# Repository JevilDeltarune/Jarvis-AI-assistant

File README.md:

# Jarvis-AI-assistant
A custom alexa type assistant using xiaozhi ai

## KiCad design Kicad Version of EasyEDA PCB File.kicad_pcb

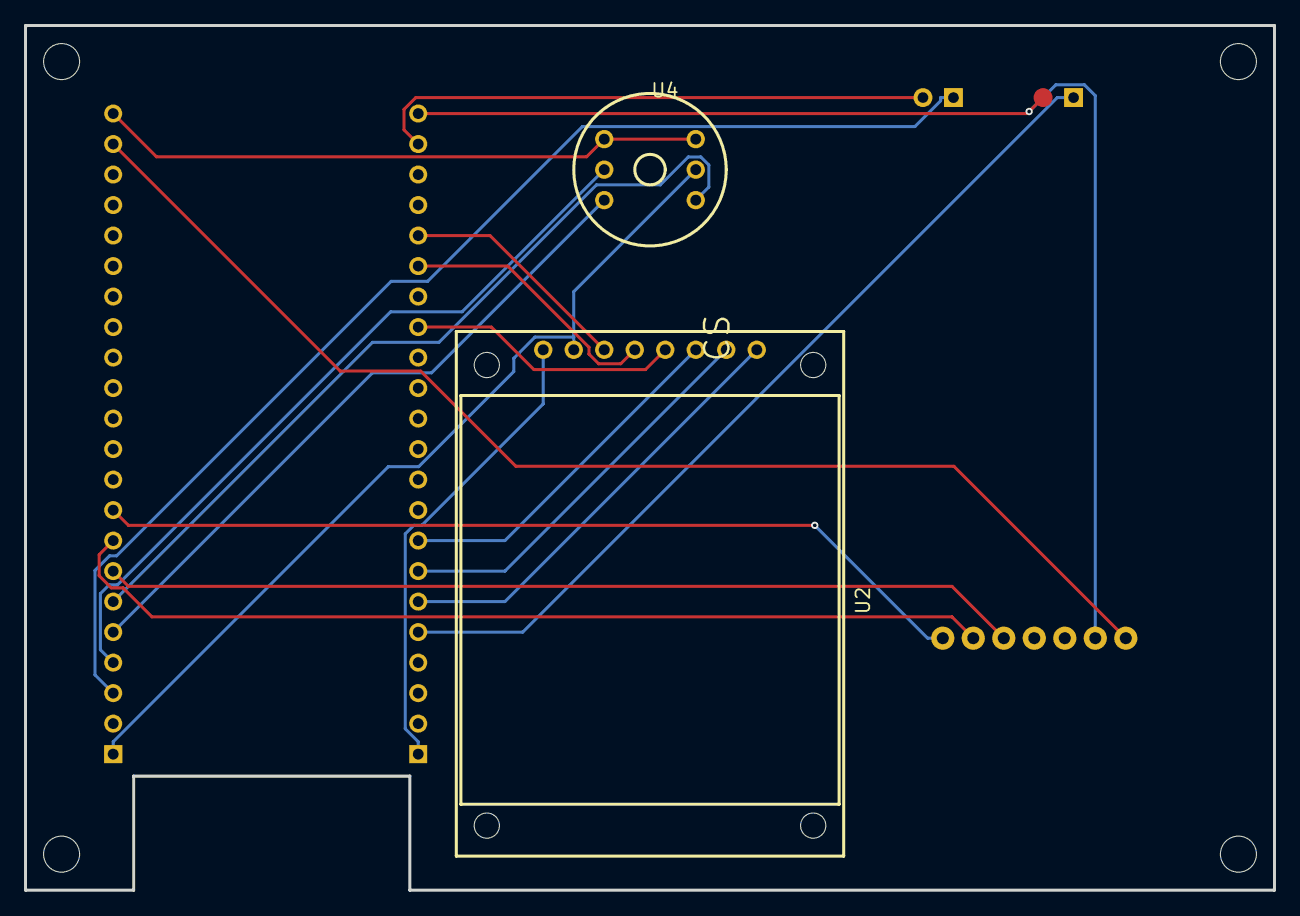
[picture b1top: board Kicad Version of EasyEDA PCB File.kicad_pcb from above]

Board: 2 copper layers, 104.0 x 72.0 mm, 6 parts (0 on the bottom side), 20 nets.

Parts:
BOOT: HDR-F-2.54_1x2; HDR-F-2.54_1X2
RESET: HDR-F-2.54_1x2; HDR-F-2.54_1X2
U1: ESP32-S3-N16R8; COMM-TH_ESP32-S3-DEVKITC-N16R8
U2: CS; 240X240 1.54 TFT SPI DISPLAY W_CS
U3: Vin; MAX98357A
U4: I2S Mic; INMP441-MEMS-I2S-MIC-MODULE

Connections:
U1_1: U1.1, U2.7, U4.2
U1_3: RESET.1, U1.3
U1_4: U1.4, U4.5
U1_5: U1.5, U4.4
U1_6: U1.6, U4.3
U1_7: U1.7, U3.5
U1_8: U1.8, U3.6
U1_9: U1.9, U3.7
U1_21: U1.21, U3.1
U1_22: U1.22, U4.1, U4.6
U1_23: BOOT.2, U1.23, U3.2
U1_24: RESET.2, U1.24
U1_27: U1.27, U2.6
U1_28: U1.28, U2.5
U1_30: U1.30, U2.4
U1_37: U1.37, U2.3
U1_38: U1.38, U2.2
U1_39: U1.39, U2.1
U1_40: BOOT.1, U1.40
U1_44: U1.44, U2.8
